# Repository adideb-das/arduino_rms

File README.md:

# arduino_rms

An Arduino sound level meter. It samples an electret microphone module at 8 kHz,
computes a running RMS, and shows the level on a 10-segment LED bar graph driven
by two cascaded 74HC595 shift registers. A browser page built on the Web Serial
API displays the same data live and lets you change the sensitivity without
opening the Arduino IDE.

## What it does

The meter computes true RMS rather than peak or envelope amplitude. It keeps a
128-sample sliding window, which is 16 ms at 8 kHz, and updates the sum of
squares incrementally, so each new sample costs the same no matter how long the
window is.

The microphone module sits on a bias of roughly 2.5 V. A first-order IIR high
pass tracks that bias and subtracts it, so the circuit needs no coupling
capacitor and corrects itself when the supply drifts.

One LED floats above the solid bar at the recent maximum. It holds there for 2
seconds, then falls at 4 segments per second.

Sensitivity changes at runtime over the serial link, so you can adapt to a
different room without reflashing.

Every 250 ms the firmware prints the raw peak-to-peak swing and the current DC
estimate, then tags the line `[MIC DEAD? A0 flat]`, `[quiet]` or
`[signal alive]`. When the display stays dark, that tag tells you whether the
microphone has failed or the room is just quiet.

## Hardware

| Part | Notes |
|---|---|
| Arduino Uno (ATmega328P, 16 MHz) | Any 5 V AVR board with an ADC works |
| KY-038 sound sensor module | Analog output only. The digital threshold pin is unused |
| 2 x 74HC595 | Cascaded, 16 outputs, 10 of them used |
| 10-segment LED bar graph | |
| 10 current-limiting resistors | 220 to 470 ohm, depending on how bright you want it |

### Pin map

| Signal | Arduino pin | 74HC595 pin |
|---|---|---|
| Audio in | A0 | |
| DATA (SER) | D11 | 14 |
| CLOCK (SRCLK) | D13 | 11 |
| LATCH (RCLK) | D10 | 12 |

D13 also drives the onboard LED on the Uno, so it flickers along with the shift
register clock. That is expected and harmless.

The schematic is in `circuit_diagram.png`. The KiCad project is under
`kicad_arduino_rms/circuit_diagram_arduino_rms/`.

## Repository layout

```
codes/
  firmware/firmware.ino          Main meter firmware
  rms-meter-monitor.html         Web Serial browser monitor
  backup/                        Duplicate of the above. See Known issues
    ky-038_calibration/          Standalone microphone diagnostic sketch
    led_bar/                     Standalone shift register and LED bar test
docs/
  setup.jpg                      Photo of the assembled hardware
  gui.png                        Screenshot of the browser monitor
kicad_arduino_rms/               KiCad schematic project
presentation/                    Project presentation slides
circuit_diagram.png              Rendered schematic
footer.png                       Slide asset used by the presentation
manual.docx                      User manual
contribution_statement.docx      Author contribution statement
```

## Getting started

### 1. Check the hardware first

Bring the two halves up separately before you run the meter. A dark display is
much harder to debug when either half might be at fault.

`codes/backup/led_bar/led_bar.ino` lights the segments 0 to 10 in sequence. If
any segment stays off, the problem is in the shift registers or the bar graph
wiring.

`codes/backup/ky-038_calibration/ky-038_calibration.ino` stays silent for 3
seconds to measure the noise floor, then prints min, max, mean and peak-to-peak
continuously at 115200 baud. A quiet room gives a peak-to-peak in the single
digits and a mean near 512. Clap and it should jump well past 100. If nothing
moves, the fault is in the microphone or its wiring, not the firmware.

### 2. Flash the meter

Upload `codes/firmware/firmware.ino` and open the Serial Monitor at 115200 baud.

### 3. Set the sensitivity

Send `+` for more sensitivity and `-` for less. The default is 120, clamped
between 10 and 1000, in steps of 10.

Inside the firmware, `sensitivity` is a divisor: `level = rms * 10 / sensitivity`.
A smaller number therefore gives a more sensitive meter, and `+` decreases it.
The serial interface hides the inversion, but the variable name reads backwards
from its arithmetic and will confuse anyone reading the source.

### 4. Browser monitor

Open `codes/rms-meter-monitor.html` in Chrome or Edge. Web Serial does not work
in Firefox or Safari. Close the Arduino Serial Monitor first so the port is
free, click Connect, and pick the board. The page parses the debug lines with
tolerant regular expressions and shows RMS, LED count, peak, DC estimate and raw
peak-to-peak. Two buttons send `+` and `-`.

## How it works

### Sampling

`loop()` compares `micros()` against `nextSampleAt` and takes one `analogRead()`
every 125 us. The deadline advances by exactly one period instead of being reset
from the current time, so timing error does not accumulate. If the loop falls
more than four periods behind, which happens whenever a debug line goes out, the
schedule resets to the present. Samples are dropped on purpose, because a burst
of catch-up reads would corrupt the RMS window.

### ADC clock

`ADCSRA` is set to a /32 prescaler, which gives a 500 kHz ADC clock and about 26
us per conversion. The default /128 prescaler runs at 125 kHz and needs roughly
104 us, leaving too little room inside a 125 us budget. Atmel specifies 50 to
200 kHz for full 10-bit accuracy, so the lowest bits are noisier than the
datasheet promises. The bar graph resolves ten steps, so that extra noise does
not limit anything you can see.

### RMS

A circular buffer of 128 `int16_t` holds the samples after DC removal. Each new
sample subtracts the outgoing square from `sumSquares` and adds the incoming
one, so nothing ever loops over the window. The length is a power of two, which
lets the index wrap with a mask instead of a modulo. Worst case `sumSquares`
reaches about 128 x 512^2, or 3.4e7, well inside a `uint32_t`.

### Display

Every 25 ms the RMS is scaled to a level between 0 and 10, rounded to a segment
count, turned into a bit pattern, and shifted out MSB first as two bytes. The
peak marker is OR-ed in only when it sits strictly above the solid bar. Peak
decay is computed from elapsed milliseconds rather than per frame, so jitter in
the display loop does not change the fall rate.

## Design parameters

| Constant | Value | Meaning |
|---|---|---|
| `SAMPLE_RATE_HZ` | 8000 | 4 kHz usable bandwidth |
| `BUF_LEN` | 128 | 16 ms RMS window. Must stay a power of two |
| `DISPLAY_PERIOD_MS` | 25 | 40 Hz refresh |
| `PEAK_HOLD_MS` | 2000 | Marker freeze before decay |
| `PEAK_DECAY_PER_SEC` | 4.0 | Segments per second |
| `sensitivity` | 120 | Divisor. Lower means more sensitive |
| `SERIAL_DEBUG` | true | Set false to remove all serial output |

## Limitations

The output is not calibrated in dB SPL. It is a relative RMS in ADC counts with
no weighting curve. Real decibels would need a reference sound source and a
known microphone sensitivity, and without A-weighting the response does not
follow how people actually hear loudness.

Usable bandwidth stops at 4 kHz. Anything above that folds back into the
measurement band, and the KY-038 has no anti-aliasing filter.

Serial debug output disturbs the sampling. A debug line at 115200 baud takes
several milliseconds to send and blocks once the 64-byte transmit buffer fills,
so a few samples vanish every 250 ms. Set `SERIAL_DEBUG` to false for the
cleanest measurement.

`shiftOut()` bit-bangs 16 bits with `digitalWrite()`, which is slow on an AVR,
and the call very likely overruns a single 125 us sample slot. It only fires
every 25 ms, so the duty is low and the sampler resyncs afterwards, but the cost
has not been measured. Hardware SPI would remove the question entirely.

## Coursework context

Built for the Complex Embedded Systems lab, MSc Micro- and Nanotechnology,
Technische Universität Ilmenau.Operating instructions are in `manual.docx`.

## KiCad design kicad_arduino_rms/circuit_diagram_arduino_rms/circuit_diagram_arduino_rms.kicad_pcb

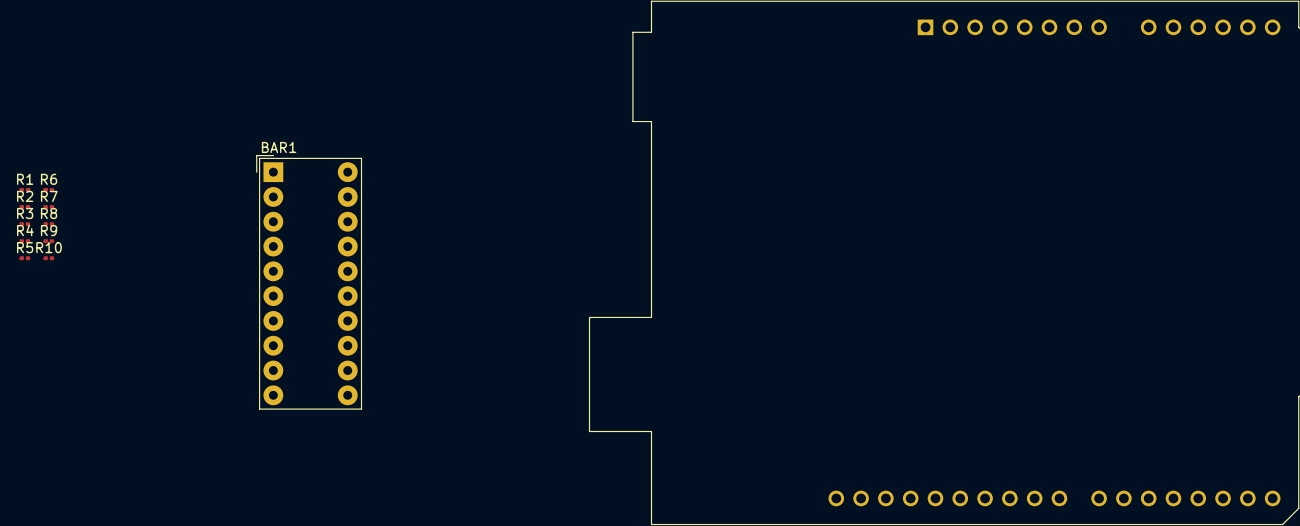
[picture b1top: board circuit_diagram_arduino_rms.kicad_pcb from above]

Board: 2 copper layers, 12 parts (0 on the bottom side), 11 nets, no tracks yet.

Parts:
A1: Arduino_UNO_R3
BAR1: HLCP-J100_2; HLCP-J100
R1, R2, R3, R4, R5, R6, R7, R8, R9, R10: 330; R_0201_0603Metric

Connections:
GND: A1.2 (IOREF), A1.3 (~RESET), A1.4 (3V3), A1.6 (GND), A1.7 (GND), A1.8 (VIN), A1.10 (A1), A1.11 (A2), A1.12 (A3), A1.13 (SDA/A4), A1.14 (SCL/A5), A1.15 (D0/RX), A1.16 (D1/TX), A1.17 (D2), A1.18 (D3), A1.19 (D4), A1.20 (D5), A1.21 (D6), A1.22 (D7), A1.23 (D8), A1.24 (D9), A1.27 (D12), A1.29 (GND), A1.30 (AREF), A1.31 (SDA/A4), A1.32 (SCL/A5), R1.2, R2.2, R3.2, R4.2, R5.2, R6.2, R7.2, R8.2, R9.2, R10.2
unnamed: BAR1.11 (K), R10.1
unnamed: BAR1.12 (K), R9.1
unnamed: BAR1.13 (K), R8.1
unnamed: BAR1.14 (K), R7.1
unnamed: BAR1.15 (K), R6.1
unnamed: BAR1.16 (K), R5.1
unnamed: BAR1.17 (K), R4.1
unnamed: BAR1.18 (K), R3.1
unnamed: BAR1.19 (K), R2.1
unnamed: BAR1.20 (K), R1.1
